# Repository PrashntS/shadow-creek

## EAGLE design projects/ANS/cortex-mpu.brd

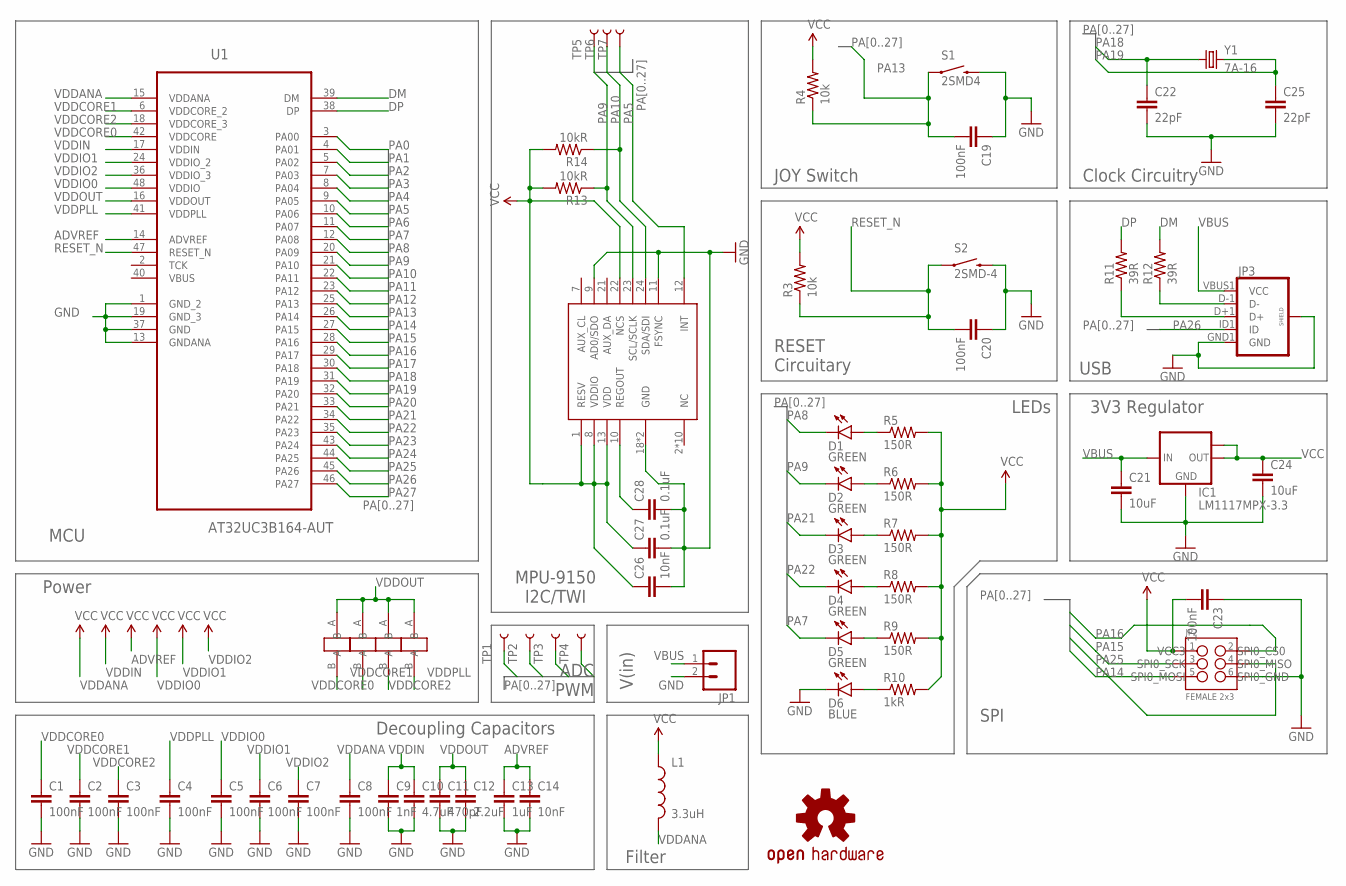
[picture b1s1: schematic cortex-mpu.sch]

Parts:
C1, C2, C3, C4, C5, C6, C7, C8, C19, C20, C23: 100nF; 0603-CAP
C9: 1nF; 0603-CAP
C10: 4.7uF; 0603-CAP
C11: 470pF; 0603-CAP
C12: 2.2uF; 0603-CAP
C13: 1uF; 0603-CAP
C14, C26: 10nF; 0603-CAP
C21, C24: 10uF; 0603-CAP
C22, C25: 22pF; 0603-CAP
C27, C28: 0.1uF; 0603-CAP
D1, D2, D3, D4, D5: GREEN; LED-0603
D6: BLUE; LED-0603
IC1: LM1117MPX-3.3; SOT223
JP1: M02LOCK; 1X02_LOCK
JP2: FEMALE 2x3; 2X3
JP3: USB_MICROB_PLUGCONN-11752; USB-B-MICRO-SMD_V03
L1: 3.3uH; 0603
LOGO1: OSHW-LOGOS-COPPER; OSHW-LOGO-S_COPPER
R3, R4: 10k; 0603-RES
R5, R6, R7, R8, R9: 150R; 0603-RES
R10: 1kR; 0603-RES
R11, R12: 39R; 0603-RES
R13, R14: 10kR; 0603-RES
S1: 2SMD4; TACTILE_SWITCH_TALL
S2: 2SMD-4; TACTILE_SWITCH_TALL
TP1, TP2, TP3, TP4, TP5, TP6, TP7: TEST-POINT2; PAD.02X.02
U1: AT32UC3B164-AUT; QFP50P900X900X120-48N
U$1, U$2, U$3, U$4: JUNCTION; JUN-2
U$5: MPU-9250; QFN-24-3MM
Y1: 7A-16; CRYSTAL-TXC-7A

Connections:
ADVREF: C13.1, C14.1, U1.14 (ADVREF)
DM: R12.2, U1.39 (DM)
DP: R11.2, U1.38 (DP)
GND: C1.2, C2.2, C3.2, C4.2, C5.2, C6.2, C7.2, C8.2, C9.2, C10.2, C11.2, C12.2, C13.2, C14.2, C19.1, C20.1, C21.2, C22.2, C23.1, C24.2, C25.2, C26.2, C27.2, C28.2, D6.C, IC1.1 (GND), JP1.2, JP2.6, JP3.GND1 (GND), JP3.SHIELD1 (SHIELD), JP3.SHIELD2 (SHIELD), JP3.SHIELD3 (SHIELD), S1.B2 (2), S2.B2 (2), U1.1 (GND_2), U1.13 (GNDANA), U1.19 (GND_3), U1.37 (GND), U$5.9 (AD0/SDO), U$5.11 (FSYNC), U$5.18 (GND), U$5.20 (GND)
unnamed: JP3.D-1 (D-), R12.1
unnamed: JP3.D+1 (D+), R11.1
unnamed: D1.A, R5.1
unnamed: D2.A, R6.1
unnamed: D6.A, R10.1
unnamed: D3.A, R7.1
unnamed: D4.A, R8.1
unnamed: D5.A, R9.1
unnamed: C28.1, U$5.10 (REGOUT)
PA0: U1.3 (PA00)
PA1: U1.4 (PA01)
PA2: U1.5 (PA02)
PA3: TP3.P$1, U1.7 (PA03)
PA4: TP4.P$1, U1.8 (PA04)
PA5: TP7.P$1, U1.9 (PA05), U$5.12 (INT)
PA6: U1.10 (PA06)
PA7: D5.C, U1.11 (PA07)
PA8: D1.C, U1.12 (PA08)
PA9: D2.C, R13.1, TP5.P$1, U1.20 (PA09), U$5.23 (SCL/SCLK)
PA10: R14.1, TP6.P$1, U1.21 (PA10), U$5.24 (SDA/SDI)
PA11: U1.22 (PA11)
PA12: U1.23 (PA12)
PA13: C19.2, R4.1, S1.A2 (1), U1.25 (PA13)
PA14: JP2.5, U1.26 (PA14)
PA15: JP2.3, U1.27 (PA15)
PA16: JP2.2, U1.28 (PA16)
PA17: U1.29 (PA17)
PA18: C22.1, U1.30 (PA18), Y1.P$1 (1)
PA19: C25.1, U1.31 (PA19), Y1.P$2 (2)
PA20: U1.32 (PA20)
PA21: D3.C, TP1.P$1, U1.33 (PA21)
PA22: D4.C, TP2.P$1, U1.34 (PA22)
PA23: U1.35 (PA23)
PA24: U1.43 (PA24)
PA25: JP2.4, U1.44 (PA25)
PA26: JP3.ID1 (ID), U1.45 (PA26)
PA27: U1.46 (PA27)
RESET_N: C20.2, R3.1, S2.A2 (1), U1.47 (RESET_N)
VBUS: C21.1, IC1.3 (IN), JP1.1, JP3.VBUS1 (VCC)
VCC: C23.2, C24.1, C26.1, C27.1, IC1.2 (OUT), IC1.TAB (OUT1), JP2.1, L1.1, R3.2, R4.2, R5.2, R6.2, R7.2, R8.2, R9.2, R10.2, R13.2, R14.2, U$5.1 (RESV), U$5.8 (VDDIO), U$5.13 (VDD), U$5.22 (NCS)
VDDANA: C8.1, L1.2, U1.15 (VDDANA)
VDDCORE0: C1.1, U1.42 (VDDCORE), U$1.B
VDDCORE1: C2.1, U1.6 (VDDCORE_2), U$2.B
VDDCORE2: C3.1, U1.18 (VDDCORE_3), U$3.B
VDDIN: C9.1, C10.1, U1.17 (VDDIN)
VDDIO0: C5.1, U1.48 (VDDIO)
VDDIO1: C6.1, U1.24 (VDDIO_2)
VDDIO2: C7.1, U1.36 (VDDIO_3)
VDDOUT: C11.1, C12.1, U1.16 (VDDOUT), U$1.A, U$2.A, U$3.A, U$4.A
VDDPLL: C4.1, U1.41 (VDDPLL), U$4.B

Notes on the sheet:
USB
3V3 Regulator
SPI0_CS0
SPI0_SCK
SPI0_MISO
SPI0_MOSI
SPI0_GND
VCC3
SPI
Clock Circuitry
RESET Circuitary
JOY Switch
LEDs
MPU-9150 I2C/TWI
Decoupling Capacitors
Filter
V(in)
ADC PWM
Power
MCU

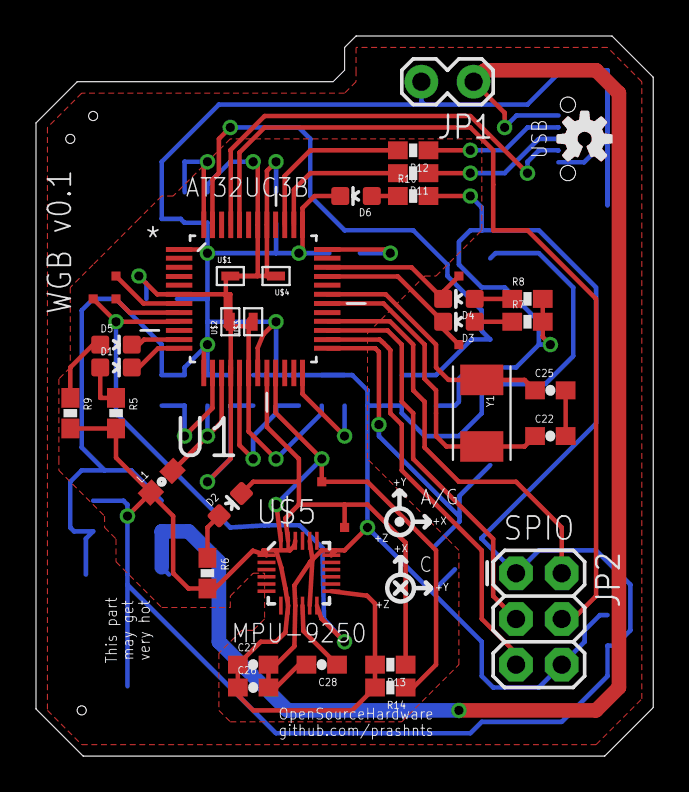
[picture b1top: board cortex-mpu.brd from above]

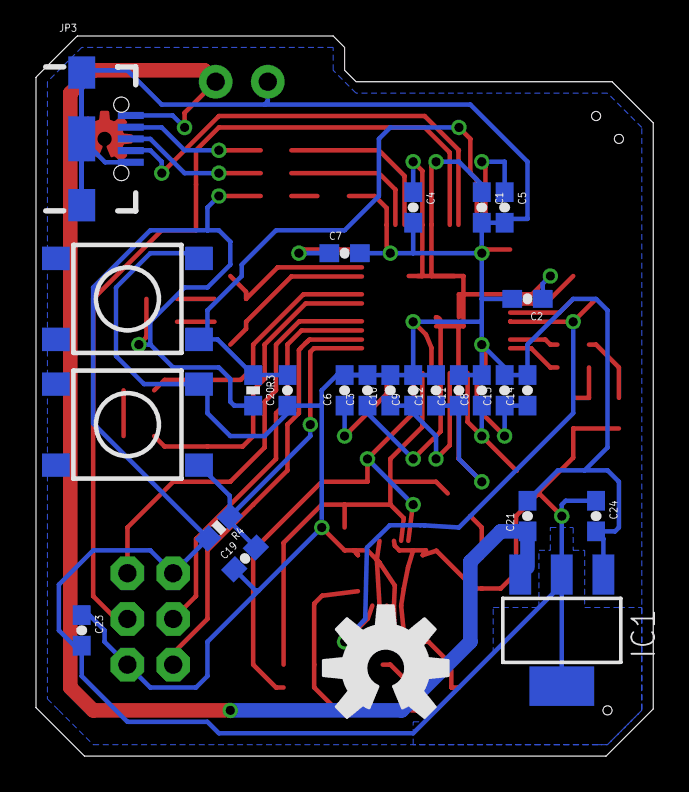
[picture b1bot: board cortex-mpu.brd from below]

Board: 2 copper layers, 34.3 x 40.0 mm, 66 parts (26 on the bottom side), 43 nets.

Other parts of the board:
U$6: OSHW-LOGO-L
U$7: OSHW-LOGO-S

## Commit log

2015-06-02 Added old project
2015-06-04 Added miRNA project
2015-06-04 miRNA Network
2015-06-04 miRNA Network Annotations
2015-06-05 Finished the miRNA Network and Poster
2015-06-06 Railways Fix the Author
2015-06-06 Fixes
2015-06-06 Seperated the files
2015-06-06 New copic lib
2015-06-09 Updated mock
2015-06-09 Fixe
2015-06-11 iPhone Mock
2015-06-13 Exports
2015-06-24 Awareness docs
2015-06-24 Awareness doc illustration
2015-06-25 Network
2015-07-01 Pixvera
2015-07-03 Added ANS
2015-07-04 Added eagle libs
2015-07-04 Added Power Regulator IC
2015-07-04 Various Net Connections
2015-07-04 Various Groups
2015-07-04 Better Grid
2015-07-04 Prelims
2015-07-05 Sm Ch
2015-07-05 Decoupling
2015-07-05 Decoupling Capr
2015-07-05 Decoupling, Changes
2015-07-06 Power line
2015-07-06 Decoupling, MPU
2015-07-07 Power conn
2015-07-07 Schematics - Done
2015-07-07 Finished
2015-07-07 Shematics, purged unneded files
2015-07-07 Fixed consistency
2015-07-07 pcb - KINDA
2015-07-08 bOARD
2015-07-08 Board layout
2015-07-08 DONE
2015-07-10 Fixed OSH logo
2015-07-10 Gerber
2015-07-17 DUWA and a few Fixes
2015-07-20 Board Fixes
2015-07-21 More fixes
2015-08-06 Multiple changes
2015-08-13 Mock
2015-08-14 Added survaider project.
2015-08-14 Moar.
2015-08-15 Uranus.
2015-09-04 Tarun
2015-09-11 Color changes.
2015-09-12 DUWA - Mag
2015-09-12 Messages
2015-09-12 Duwa

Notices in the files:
parts and their libraries:
SparkFun-Passives: Licensing: Creative Commons ShareAlike 4.0 International - https://creativecommons.org/licenses/by-sa/4.0
